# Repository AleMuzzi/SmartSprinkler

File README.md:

# SmartSprinkler

Autonomous irrigation system with Bayesian decision-making, ESP32 relay control, and a mobile app for manual override.

## Architecture

```mermaid
graph TB
    subgraph "ESP32 (C++ / PlatformIO)"
        SENSORS["HW-390 soil moisture<br/>DHT22 temp/humidity"]
        PUMP["Water pump relay (GPIO 12)"]
        API_ESP["HTTP API (:80)<br/>GET /status<br/>POST /command"]
    end

    subgraph "Mobile App (Flutter)"
        HOME["Home — Start/Stop irrigation<br/>toggle Bayesian routing"]
        SETTINGS["Settings — ESP URL +<br/>Bayesian server URL"]
    end

    subgraph "BayesianSprinkler (Python / FastAPI)"
        WX["Open-Meteo API<br/>cloud cover + rain forecast"]
        BN["Bayesian Network<br/>EvaporationRisk → NeedWater"]
        DB[("SQLite<br/>sensor_history")]
        API_BS["HTTP API (:8080)<br/>POST /api/plants/manual-water<br/>GET /api/health"]
        WORKER["APScheduler<br/>inference cycle (30 min)"]
        REFINE["refine_weights.py<br/>Bayesian estimation<br/>(cron weekly)"]
    end

    SENSORS --> API_ESP
    API_ESP --> API_BS
    API_ESP --> HOME

    HOME -->|"toggle ON"| API_BS
    HOME -->|"toggle OFF"| API_ESP
    SETTINGS --> HOME

    API_BS -->|reads + waters| API_ESP
    API_BS --> WX
    API_BS --> DB
    WORKER --> API_ESP
    WORKER --> WX
    WORKER --> BN
    WORKER --> DB
    REFINE --> DB
    REFINE -.->|updates| BN
```

## Components

### [`firmware/`](firmware) — ESP32 controller

PlatformIO project running on an ESP32-CAM. Exposes two HTTP servers:

- **Smart Sprinkler API** (Mongoose, port 80):
  - `GET /status` — returns `air_temperature`, `air_humidity`, `soil_moisture`, `water_pump`
  - `POST /command` — accepts `{"action": "START|STOP|DISPENSE_SPECIFIC_AMOUNT", "target": "PLANT_NAME", "amount": <ml>}` and toggles the pump relay on GPIO 12
  - `GET /health` — `{"status":"ok", "version":"<FW_VERSION>"}` (auto-incremented per build)
  - `POST /update` — OTA firmware upload (`multipart/form-data`, `update=firmware.bin`)

### [`smartsprinkler_app/`](smartsprinkler_app) — Flutter mobile app

ViewModel-based app with 4 tabs (Dashboard, Camera, Logs, System). It polls the Bayesian server's `/api/dashboard` (the ESP's latest captured snapshot, no direct ESP polling) and lets the user:

- Select a plant from a dropdown
- Start/Stop irrigation via `POST /command` directly to the ESP, **or** route through the Bayesian server (toggle switch)
- Monitor the cistern level, view the audit log (with errors), watch the live ESP camera, and receive water-low notifications
- Configure internal (LAN) and external URL pairs per service in Settings — the app auto-switches based on the active Wi-Fi SSID

### [`BayesianSprinkler/`](BayesianSprinkler) — Python Bayesian server

FastAPI server that runs the autonomous decision loop:

- **Bayesian network** with 8 nodes (`AirTemperature`, `AirHumidity`, `CloudCover` → `EvaporationRisk` → `NeedWater` + `SoilMoisture`, `PlantType`, `RainForecast`). Intermediate `EvaporationRisk` node keeps CPTs compact (18 + 72 entries).
- **APScheduler** runs a single background job every `poll_interval` seconds (30 min by default):
  - *Inference cycle* — reads the ESP sensors, fetches weather, logs every plant's BN decision (`need_water=yes/no` per plant) to SQLite, then waters plants that exceed their probability threshold
- **`POST /api/plants/manual-water`** — on-demand endpoint called by the mobile app: snapshots current conditions with `need_water=yes`, then triggers the ESP relay
- **Cistern tracking** — the server tracks the water tank level (`/api/cistern`), deduces refills from the ESP `water_low_alert` sensor, and provides `POST /api/cistern/refill` for manual override
- **Audit log** — every inference, command, and error is logged with a traceback (`/api/audit-log`, `GET`/`DELETE`/CSV export); errors are surfaced in the web UI instead of silently swallowed
- **OTA relay** — `POST /api/esp/ota` streams a firmware `.bin` upload on to the ESP's `/update` (with audit logging), and `GET /api/esp/version` relays the installed firmware version read from the ESP `/health` endpoint
- **`refine_weights.py`** — Bayesian parameter estimation with Dirichlet prior, blends expert CPTs with collected data to refine the model over time

## Data flow

```
                    ┌──────────────────────┐
                    │   Mobile App          │
                    │  (manual override)    │
                    └──┬───────────────┬────┘
                       │ toggle OFF    │ toggle ON
                       ▼               ▼
              ┌────────────────┐  ┌──────────────────┐
              │  ESP32 (:80)   │  │ BayesianSprinkler │
              │  GET /status   │  │  (:8080)          │
              │  POST /command │  │  POST /manual-    │
              └────────────────┘  │  water            │
                       ▲          └────────┬─────────┘
                       │                   │
                       │            ┌──────▼──────┐
                       │            │  Open-Meteo  │
                       │            │  (weather)   │
                       │            └─────────────┘
                       │
              ┌────────┴────────┐
              │  SQLite          │
              │  sensor_history  │
              └────────┬────────┘
                       │
              ┌────────▼────────┐
              │  refine_weights │──► updated BN CPTs
              │  (cron weekly)  │
              └─────────────────┘
```

## Testing

```bash
cd BayesianSprinkler
uv sync
uv run pytest          # full suite: BN, API, ESP integration, firmware API contract
```

The firmware API contract tests (`tests/test_firmware_api_contract.py`) emulate Mongoose's chunked HTTP send against the exact `/status`, `/health`, and `/command` schemas, so the server client fails loudly if the ESP ever regresses to a truncated/invalid JSON body.

## Quick start

```bash
# Bayesian server
cd BayesianSprinkler
uv sync
uv run bayesian-sprinkler

# Mobile app
cd smartsprinkler_app
flutter run

# Firmware (requires PlatformIO)
cd firmware
pio run --target upload
```

See each component's README for detailed setup instructions.

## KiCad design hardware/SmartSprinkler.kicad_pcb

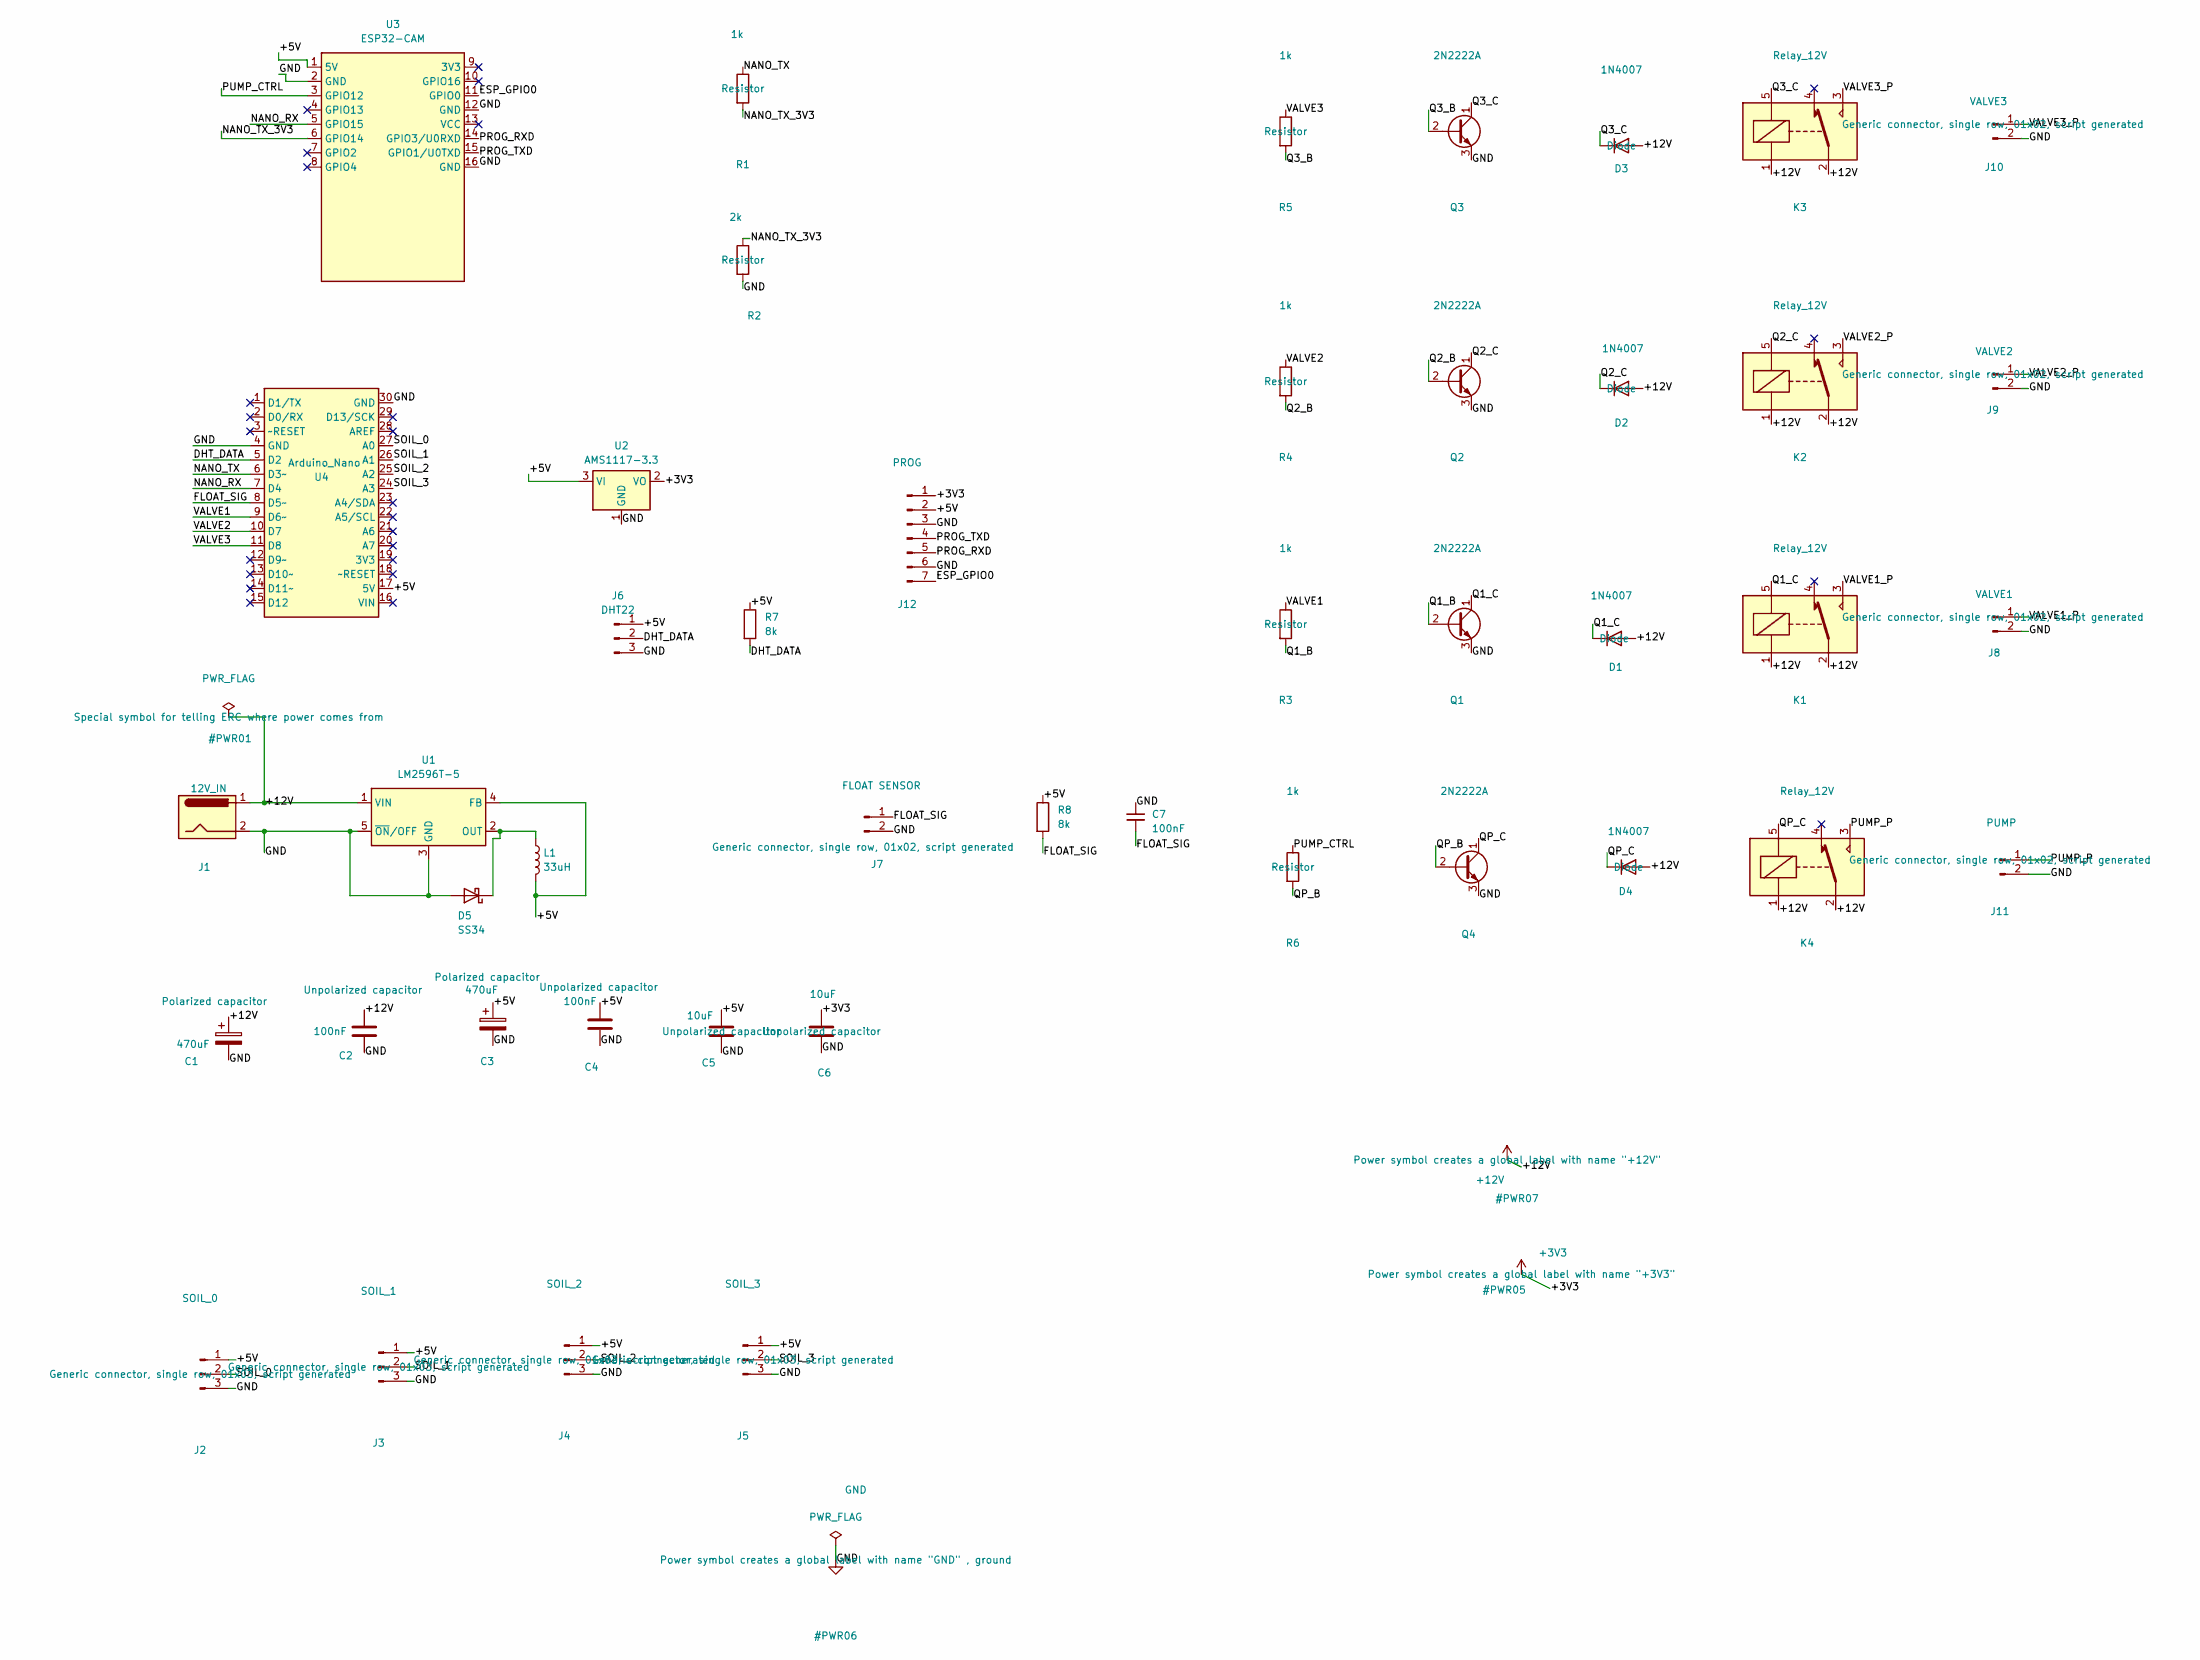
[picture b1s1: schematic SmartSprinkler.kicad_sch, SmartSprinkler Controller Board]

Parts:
C1, C3: 470uF; CP_Radial_D8.0mm_P3.50mm
C2, C4: 100nF; C_Disc_D4.7mm_W2.5mm_P5.00mm
C5, C6: 10uF; CP_Radial_D5.0mm_P2.00mm
C7: 100nF; CP_Radial_D5.0mm_P2.00mm
D1, D2, D3, D4: 1N4007; D_DO-41_SOD81_P10.16mm_Horizontal
D5: SS34; D_SMA
J1: 12V_IN; BarrelJack_Horizontal
J2: SOIL_0; PinHeader_1x03_P2.54mm_Vertical
J3: SOIL_1; PinHeader_1x03_P2.54mm_Vertical
J4: SOIL_2; PinHeader_1x03_P2.54mm_Vertical
J5: SOIL_3; PinHeader_1x03_P2.54mm_Vertical
J6: DHT22; PinHeader_1x03_P2.54mm_Vertical
J7: FLOAT SENSOR; PinHeader_1x02_P2.54mm_Vertical
J8: VALVE1; PinHeader_1x02_P2.54mm_Vertical
J9: VALVE2; PinHeader_1x02_P2.54mm_Vertical
J10: VALVE3; PinHeader_1x02_P2.54mm_Vertical
J11: PUMP; PinHeader_1x02_P2.54mm_Vertical
J12: PROG; PinHeader_1x07_P2.54mm_Vertical
K1, K2, K3, K4: Relay_12V; Relay_SPDT_Omron-G5Q-1
L1: 33uH; L_Axial_L13.0mm_D4.5mm_P5.08mm_Vertical_Fastron_HCCC
Q1, Q2, Q3, Q4: 2N2222A; TO-92_Inline
R1, R3, R4, R5, R6: 1k; R_Axial_DIN0207_L6.3mm_D2.5mm_P10.16mm_Horizontal
R2: 2k; R_Axial_DIN0207_L6.3mm_D2.5mm_P10.16mm_Horizontal
R7, R8: 8k; R_Axial_DIN0207_L6.3mm_D2.5mm_P10.16mm_Horizontal
U1: LM2596T-5; TO-220-5_P3.4x3.7mm_StaggerOdd_Lead3.8mm_Vertical
U2: AMS1117-3.3; SOT-223-3_TabPin2
U3: ESP32-CAM
U4: Arduino_Nano

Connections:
+3V3: C6.1, J12.1, U2.2 (VO)
+12V: C1.1, C2.1, D1.2 (A), D2.2 (A), D3.2 (A), D4.2 (A), J1.1, K1.1, K1.2, K2.1, K2.2, K3.1, K3.2, K4.1, K4.2, U1.1 (VIN)
/+5V: C3.1, C4.1, C5.1, J2.1, J3.1, J4.1, J5.1, J6.1, J12.2, L1.2, R7.1, R8.1, U1.4 (FB), U2.3 (VI), U3.1 (5V), U4.17 (5V)
/DHT_DATA: J6.2, R7.2, U4.5 (D2)
/ESP_GPIO0: J12.7, U3.11 (GPIO0)
/FLOAT_SIG: C7.2, J7.1, R8.2, U4.8 (D5~)
/NANO_RX: U3.5 (GPIO15), U4.7 (D4)
/NANO_TX: R1.1, U4.6 (D3~)
/NANO_TX_3V3: R1.2, R2.1, U3.6 (GPIO14)
/PROG_RXD: J12.5, U3.14 (GPIO3/U0RXD)
/PROG_TXD: J12.4, U3.15 (GPIO1/U0TXD)
/PUMP_CTRL: R6.1, U3.3 (GPIO12)
/PUMP_P: J11.1, K4.3
/Q1_B: Q1.2 (B), R3.2
/Q1_C: D1.1 (K), K1.5, Q1.1 (C)
/Q2_B: Q2.2 (B), R4.2
/Q2_C: D2.1 (K), K2.5, Q2.1 (C)
/Q3_B: Q3.2 (B), R5.2
/Q3_C: D3.1 (K), K3.5, Q3.1 (C)
/QP_B: Q4.2 (B), R6.2
/QP_C: D4.1 (K), K4.5, Q4.1 (C)
/SOIL_0: J2.2, U4.27 (A0)
/SOIL_1: J3.2, U4.26 (A1)
/SOIL_2: J4.2, U4.25 (A2)
/SOIL_3: J5.2, U4.24 (A3)
/VALVE1: R3.1, U4.9 (D6~)
/VALVE1_P: J8.1, K1.3
/VALVE2: R4.1, U4.10 (D7)
/VALVE2_P: J9.1, K2.3
/VALVE3: R5.1, U4.11 (D8)
/VALVE3_P: J10.1, K3.3
GND: C1.2, C2.2, C3.2, C4.2, C5.2, C6.2, C7.1, D5.2 (A), J1.2, J2.3, J3.3, J4.3, J5.3, J6.3, J7.2, J8.2, J9.2, J10.2, J11.2, J12.3, J12.6, Q1.3 (E), Q2.3 (E), Q3.3 (E), Q4.3 (E), R2.2, U1.3 (GND), U1.5 (~ON/OFF), U2.1 (GND), U3.2 (GND), U3.12 (GND), U3.16 (GND), U4.4 (GND), U4.30 (GND)
unnamed: D5.1 (K), L1.1, U1.2 (OUT)

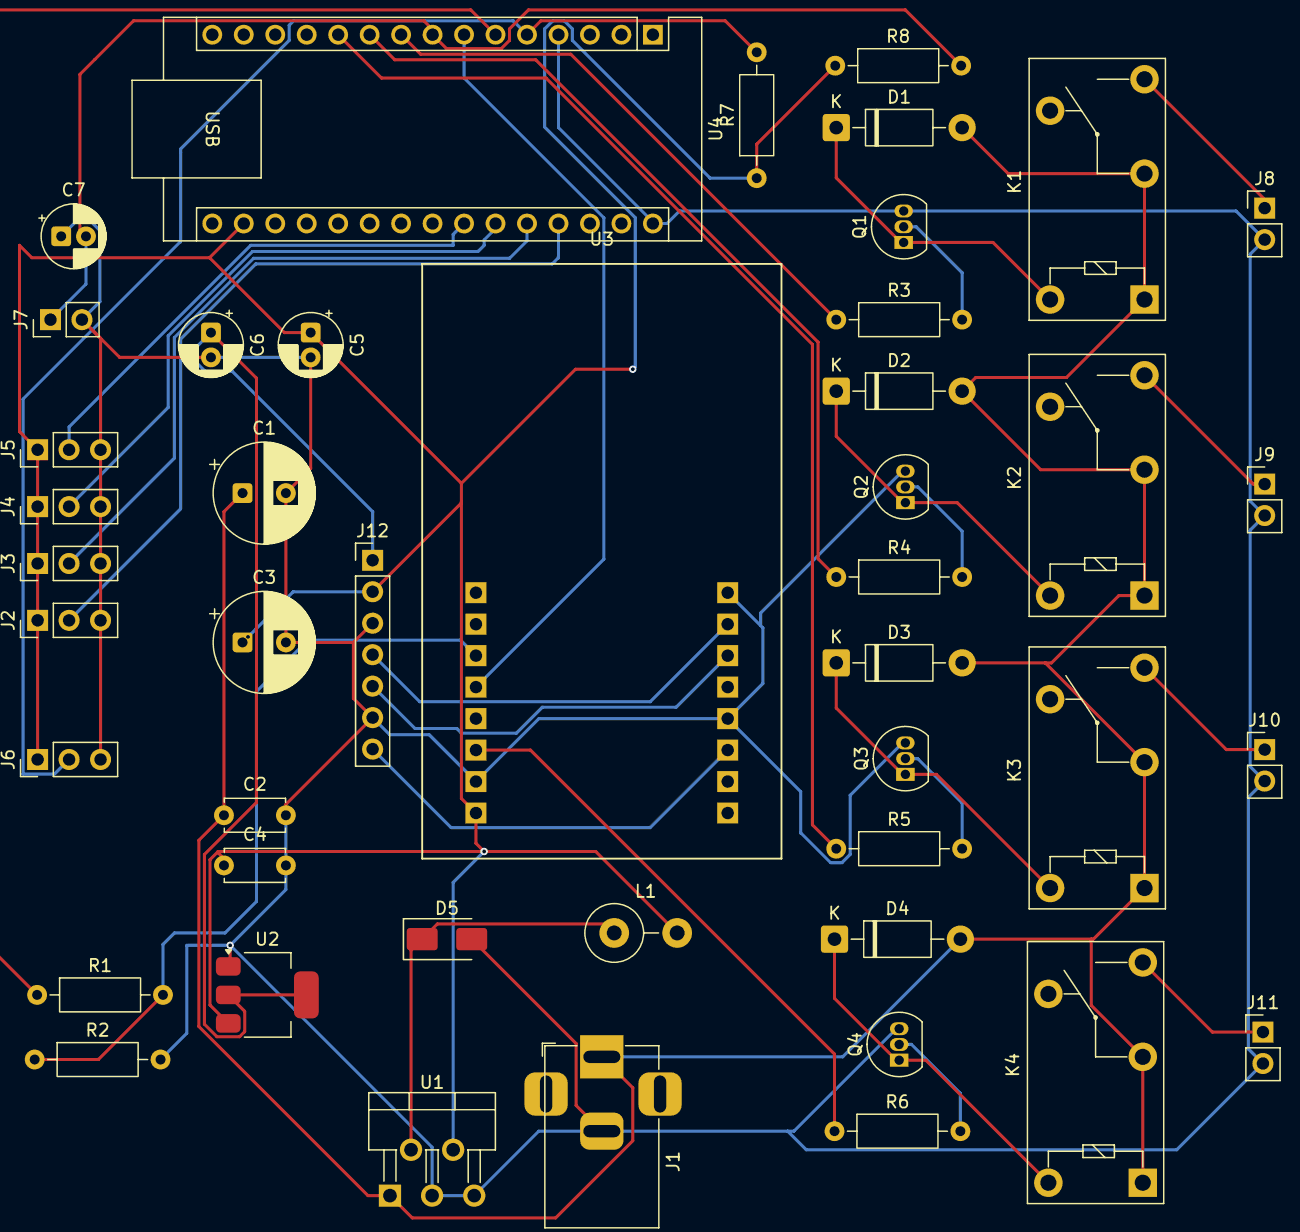
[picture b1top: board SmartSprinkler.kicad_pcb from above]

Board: 2 copper layers, 45 parts (0 on the bottom side), 33 nets.

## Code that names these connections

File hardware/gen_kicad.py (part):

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     "x": 251.46, "y": 236.22, "nets": {"1": "NANO_TX_3V3", "2": "GND"}},
    
    # Soil sensors
    {"ref": "J2", "lib": "Connector", "sym": "Conn_01x03_Pin", "val": "SOIL_0",
     "fp": "Connector_PinHeader_2.54mm:PinHeader_1x03_P2.54mm_Vertical",
     "x": 45.72, "y": 271.78, "nets": {"1": "+5V_RAW", "2": "SOIL_0", "3": "GND"}},
    {"ref": "J3", "lib": "Connector", "sym": "Conn_01x03_Pin", "val": "SOIL_1",
     "fp": "Connector_PinHeader_2.54mm:PinHeader_1x03_P2.54mm_Vertical",
     "x": 101.6, "y": 271.78, "nets": {"1": "+5V_RAW", "2": "SOIL_1", "3": "GND"}},
    {"ref": "J4", "lib": "Connector", "sym": "Conn_01x03_Pin", "val": "SOIL_2",
     "fp": "Connector_PinHeader_2.54mm:PinHeader_1x03_P2.54mm_Vertical",
     "x": 157.48, "y": 271.78, "nets": {"1": "+5V_RAW", "2": "SOIL_2", "3": "GND"}},
    {"ref": "J5", "lib": "Connector", "sym": "Conn_01x03_Pin", "val": "SOIL_3",
     "fp": "Connector_PinHeader_2.54mm:PinHeader_1x03_P2.54mm_Vertical",
     "x": 213.36, "y": 271.78, "nets": {"1": "+5V_RAW", "2": "SOIL_3", "3": "GND"}},
    
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    {"ref": "K1", "lib": "Relay", "sym": "Relay_SPDT", "val": "Relay_12V",
     "fp": "Relay_THT:Relay_SPDT_Hongfa_HF32F-G_5V",
     "x": 393.7, "y": 101.6, "nets": {"1": "Q1_C", "2": "+12V", "3": "VALVE1_P", "4": "+12V", "5": "NC"}},
    {"ref": "J8", "lib": "Connector", "sym": "Conn_01x02_Pin", "val": "VALVE1",
     "fp": "Connector_PinHeader_2.54mm:PinHeader_1x02_P2.54mm_Vertical",
     "x": 444.5, "y": 101.6, "nets": {"1": "VALVE1_P", "2": "GND"}},
    
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    {"ref": "K2", "lib": "Relay", "sym": "Relay_SPDT", "val": "Relay_12V",
     "fp": "Relay_THT:Relay_SPDT_Hongfa_HF32F-G_5V",
     "x": 393.7, "y": 41.91, "nets": {"1": "Q2_C", "2": "+12V", "3": "VALVE2_P", "4": "+12V", "5": "NC"}},
    {"ref": "J9", "lib": "Connector", "sym": "Conn_01x02_Pin", "val": "VALVE2",
     "fp": "Connector_PinHeader_2.54mm:PinHeader_1x02_P2.54mm_Vertical",
     "x": 444.5, "y": 41.91, "nets": {"1": "VALVE2_P", "2": "GND"}},
    
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    {"ref": "K3", "lib": "Relay", "sym": "Relay_SPDT", "val": "Relay_12V",
     "fp": "Relay_THT:Relay_SPDT_Hongfa_HF32F-G_5V",
     "x": 393.7, "y": -17.78, "nets": {"1": "Q3_C", "2": "+12V", "3": "VALVE3_P", "4": "+12V", "5": "NC"}},
    {"ref": "J10", "lib": "Connector", "sym": "Conn_01x02_Pin", "val": "VALVE3",
     "fp": "Connector_PinHeader_2.54mm:PinHeader_1x02_P2.54mm_Vertical",
     "x": 444.5, "y": -17.78, "nets": {"1": "VALVE3_P", "2": "GND"}},
    
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
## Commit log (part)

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2025-08-23 Initial commit - working on ESP32
    - Added Mongoose HTTP server
    - Added support for commands
    - Added unused UDP server
2025-08-23 Cleanup
    - Moved camera management to its own file
    - Moved board pinout to its own file
    - Added safety check on amount param in command
2025-08-31 Enhanced HTTP routes management
2025-09-09 First end-to-end working with commands
    - Implemented water pump actuator
    - Fixed wifi connection
    - Added /health route
    - Added /command route
    - Enhanced /status route
    - Changed payload type recognization system
2025-09-09 Adjusted /status payload keys
2025-09-09 Init for app
    First version of a working app, provided with:
    - Settings to change the sprinkler endpoint
    - Home with:
    - sensor readings
    - Start/stop commands
2025-09-10 Removed redundant toast
2025-09-11 Added soil moisture sensor (not working due to ADC2 shared with WiFi issue)
    - Removed verbose Hashtable debug prints
    - Internalized Hashtable lib
    - Cleaned up console
2025-09-11 Some adjustments
    - Updated app's icon
    - Added soil moisture reading (but kept commented in the UI for now)
    - Increased polling frequency 1s -> 2s
2026-05-15 Reorganized firmware files
2026-05-15 New BayesianSprinkler repo
    Here's a summary of all changes across the entire conversation, organized by directory:
    ---
    ### New directory: `BayesianSprinkler/`
    **Core Bayesian network:**
    - `pyproject.toml` — project config, uv-based, deps: pgmpy, fastapi, uvicorn, apscheduler, pandas
    - `config.yaml` — ESP connection, weather API coords, discretization thresholds, 4 plant configs with per-plant `base_need`, `threshold`, `watering_duration`
2026-05-15 Adjusted READMEs
2026-05-20 Valve routing, Arduino Nano sensor hub, Naga Morich rename
    - Add 3-valve binary cascade plumbing to route water to 4 plants
    (Habanero, Naga Morich, Carolina Reaper, Rosmarino)
    - Implement DISPENSE_SPECIFIC_AMOUNT with flow-rate-based timed dispensing
    - Fix double-response bug in POST /command handler
    - Enrich GET /status with valve states and active plant name
    - Add Arduino Nano as UART sensor co-processor reading 4 HW-390 sensors
2026-05-21 Replace Arduino Nano with ADS1115, clean up camera LED handler
    - Remove Arduino Nano UART sensor co-processor and [env:nano] target
    (deleted: firmware/arduino_nano/src/main.cpp, platformio.ini section)
    - Add ADS1115 4-channel 16-bit ADC on software I2C (GPIO 14=SDA, GPIO 4=SCL)
    - Add Adafruit ADS1X15 library dependency to platformio.ini
    - Replace request/response UART protocol with direct I2C reads in main.cpp
    - Remove /ledon and /ledoff HTTP handlers from app_httpd.cpp
2026-05-21 Add water level alert system, unit tests, and integration tests
    - Firmware: add water_low_alert guard on START/DISPENSE; Command.force
    field bypasses alert; /status returns water_low_alert + blocked_amount_ml
    - Bayesian server: check water_low_alert in manual_water and
    _inference_cycle; return 503 when blocked
    - Flutter: LowWaterAlertPage with force-water override; warning banner
    on home page when alert active; Sprinkler model updated
2026-05-21 Replace 3-electrovalve binary cascade with SG90 rotary selector
    - Replaced V1/V2/V3 valve relays with SG90 servo on GPIO 13 driven by
    ESP32Servo library; plant selection now maps to 0/15/30/45° positions
    - Added plant_to_servo() and move_servo_to_position() with calibration
    sweep on startup (≤100µs tolerance per position)
    - /status returns rotary_position (0-3 or "uncalibrated") and active_plant
    - Removed valve pinouts and routing from firmware; water_low_alert unchanged
2026-05-21 Fix servo library name, attach signature, and bottom section overflow
    - platformio.ini: madhephaestus/ESP32Servo @ ^3.2.0 (was espressif/ESP32Servo)
    - main.cpp: Servo::attach(pin, min, max) 3-arg form (was 4-arg with freq)
    - home.dart: wrap bottom Container in Expanded + Column.mainAxisSize.min to fix
    RenderFlex overflow on smaller test viewport sizes
2026-05-21 Redesign Flutter UI: dashboard, plant detail, system control views
    - Replace dropdown/toggle UI with data-visualization-focused dashboard:
    - Top: SfRadialGauge showing avg probability of need across all plants
    - Middle: horizontal PageView plant cards with CachedNetworkImage, prob%, Water Now button
    - Bottom: weather conditions footer (temp, humidity, rain, clouds)
    - Add PlantDetailView: soil moisture bar, probability gauge, Bayesian insights
    ExpansionTile showing evidence node scoring breakdown
2026-05-21 Add local plant images for cards
    - Download habanero, naga_morich, carolina_reaper, rosmarino images via picsum
    - Add assets/images/ to pubspec.yaml
    - Switch from CachedNetworkImage to local Image.asset for cards
    - Remove cached_network_image dependency (no longer needed)
2026-05-21 Fixed plant images
2026-05-21 Added docker deployment
2026-05-21 Adjusted servo motor angles
2026-05-21 Dynamic adaptive polling based on air temperature
    - APScheduler hourly poll now dynamically reschedules its own interval
    based on current temperature: low (<16°C) → 60 min, medium (16-29°C) →
    30 min, high (≥29°C) → 15 min
    - Use IntervalTrigger + scheduler.modify_job() under AppState.lock to avoid
    race conditions when rescheduling the active job
    - WeatherClient now fetches temperature_2m from Open-Meteo; if ESP is
2026-05-21 Add BN validation framework, auto-adjuster, and containerized weekly cron
    - Add validate_network.py: K-fold CV (Precision/Recall/F1/ROC-AUC/Brier), sensitivity
    analysis (mutual info rank, axiomatic sweeps), structured markdown report
    - Add auto_adjuster.py: reads report, adjusts CPT base_need per plant (±25% cap)
    based on Brier/recall/precision thresholds and soil_wet/rain suppression checks
    - Add scripts/cron_validator.sh: daily wrapper with ≥6-day interval guard and
    lockfile protection (for local dev; container cron uses supercronic)
2026-05-24 Fix manual override fallback, firmware test deps, add container cron for BN validation
2026-05-27 Calibrated rotary selector
2026-05-27 Fixed bayesian server deployment
2026-05-28 Fixed app overflow
2026-05-28 Fixed /api/plants/status API and added swagger docs
2026-05-28 Fix async dispose crash, polling frequency, settings UX, and add weather cache
    Backend:
    - Poll weather API every 30s and cache result in AppState
    - /api/plants/status now uses cached weather instead of fetching on demand
    - /api/weather/status returns cached weather data
    App:
    - Add _disposed flag + _notify() helper to prevent notifyListeners after dispose
2026-05-28 Fixed humidity percentage range issue in app
2026-05-28 Added bayesian factors explanation
2026-05-28 Removed operation mode in favor of an on-demand dialog
2026-05-28 Undo sensor pin changed
2026-05-29 Removed old unused code
2026-06-01 Added web portal for Bayesian server
2026-06-25 Diversi bugfix
    - ESP firmware: flow rate corretto (1380 ml/min), DISPENSE_SPECIFIC_AMOUNT non-bloccante (main loop stop), camera_url in /status, buffer header CORS 64→256 byte
    - Flutter app: polling 2s→10s, fix doppie richieste (ViewModel condiviso), rimosso auto-stop 20s, aggiunto dispenseAmount() con UI (campo ml + preset 50/100/200), settings con Save button sempre visi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
    - Web frontend: già supporta erogazione quantità
    - platformio: aggiunte librerie mancanti a esp32_no_cam
